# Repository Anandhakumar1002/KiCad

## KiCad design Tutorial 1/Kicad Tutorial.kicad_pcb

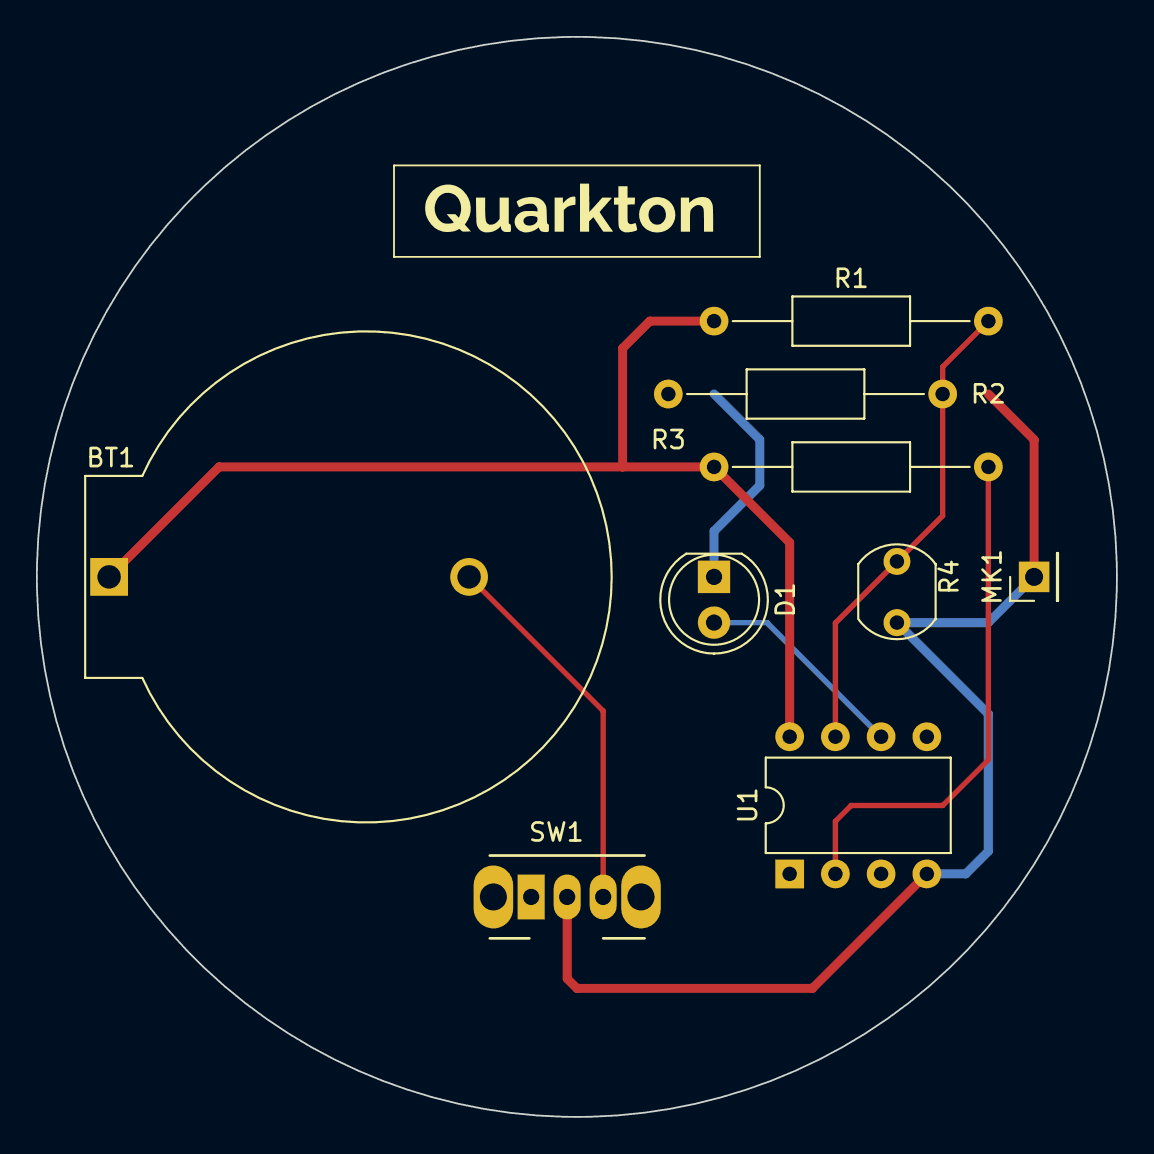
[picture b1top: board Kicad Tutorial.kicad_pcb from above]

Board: 2 copper layers, 60.0 x 60.0 mm, 9 parts (0 on the bottom side), 7 nets.

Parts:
BT1: 3.3V Cell; BatteryHolder_ComfortableElectronic_CH273-2450_1x2450
D1: LED; LED_D5.0mm
MK1: Microphone_Condenser; PinHeader_1x01_P2.54mm_Vertical
R1: 10k; R_Axial_DIN0207_L6.3mm_D2.5mm_P15.24mm_Horizontal
R2: 470R; R_Axial_DIN0207_L6.3mm_D2.5mm_P15.24mm_Horizontal
R3: 5.6k; R_Axial_DIN0207_L6.3mm_D2.5mm_P15.24mm_Horizontal
R4: LDR07; R_LDR_5.1x4.3mm_P3.4mm_Vertical
SW1: SW_SPDT; SW_CuK_OS102011MA1QN1_SPDT_Angled
U1: ATtiny85V-10P; DIP-8_W7.62mm

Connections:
+3.3V: BT1.1 (+), R1.1, R3.1, U1.8 (VCC)
/LDR: R1.2, R4.1, U1.7 (PB2)
/LED: D1.2 (A), U1.6 (PB1)
/L_TO_R: D1.1 (K), R2.1
/MIC: R3.2, U1.2 (XTAL1/PB3)
GND: MK1.1 (-), R2.2, R4.2, SW1.2 (B), U1.4 (GND)
unnamed: BT1.2 (-), SW1.3 (C)

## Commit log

2025-05-05 new files
2025-05-05 new update
2025-05-06 modified
2025-05-12 new updates upto 10
2025-05-13 completed
2025-05-13 images
